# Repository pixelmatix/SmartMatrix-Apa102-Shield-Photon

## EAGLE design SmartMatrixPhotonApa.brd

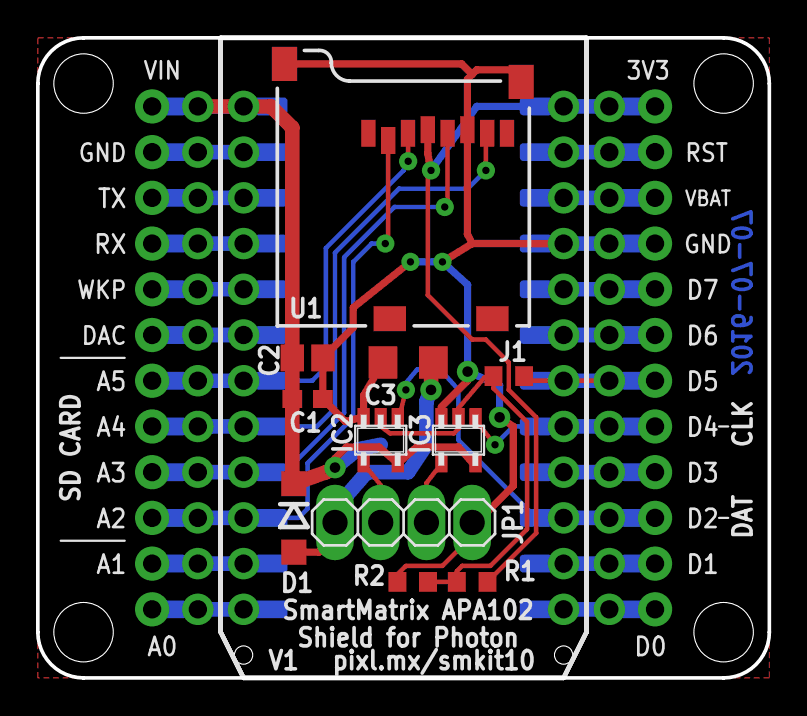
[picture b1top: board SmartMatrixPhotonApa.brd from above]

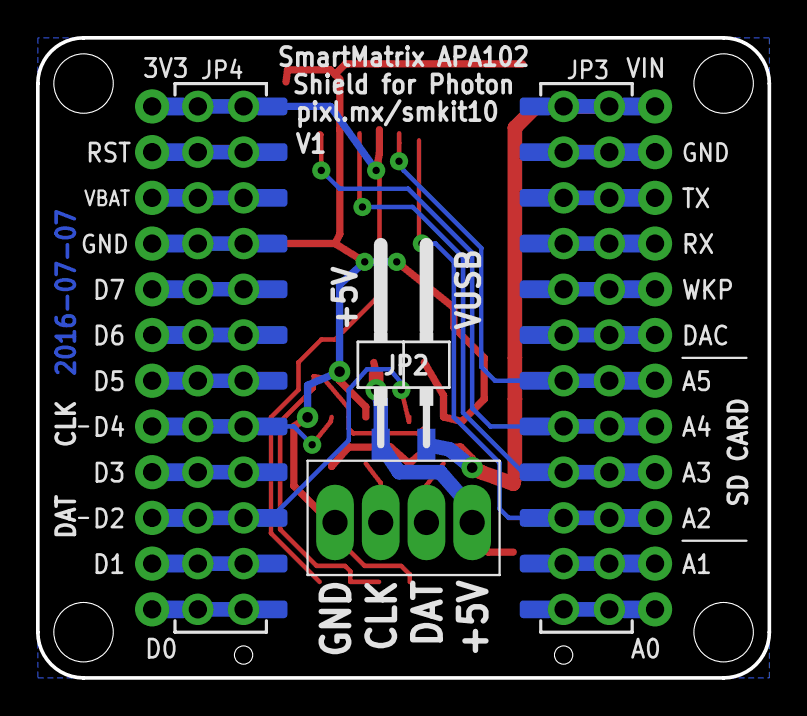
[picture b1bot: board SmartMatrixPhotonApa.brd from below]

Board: 2 copper layers, 40.6 x 35.6 mm, 14 parts (3 on the bottom side), 28 nets.

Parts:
C1: 0.1uF; C0603
C2: 10uF; C0805
C3: 100uF; C1206
D1: MBR0520LT; SOD123
IC1, IC2: 74AHC1G08DBV; SOT23-5
J1: 0-DNP; R0603
JP1: 1X04-LARGEHOLE
JP2: 1X02SMD/90
JP3: 2x12 Female SMT Socket; PHOTON_DUAL_HEADER_SHIELD_BOT_MOUNT_LEFT
JP4: 2x12 Female SMT Socket; PHOTON_DUAL_HEADER_SHIELD_BOT_MOUNT_RIGHT
R1: 47k; R0603
R2: 47k-DNP; R0603
U1: microSD; MICRO-SD-SOCKET-PP

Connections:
3V3: JP4.1, JP4.2, JP4.3V3, R1.1, U1.4
CLK: IC2.4, JP1.3
DAT: IC1.4, JP1.2
GND: C1.2, C2.2, C3.2, IC1.3, IC2.3, JP1.4, JP4.7, JP4.8, JP4.GND@2, R2.2, U1.6, U1.GND1, U1.GND2
LED_CLK: IC2.1, JP4.15, JP4.16, JP4.D4
LED_DAT: IC1.1, JP4.19, JP4.20, JP4.D2
LED_EN: J1.1, JP4.13, JP4.14, JP4.D5
unnamed: JP3.3, JP3.4, JP3.GND@0
unnamed: JP3.5, JP3.6, JP3.TX
unnamed: JP3.7, JP3.8, JP3.RX
unnamed: IC1.2, IC2.2, J1.2, R1.2, R2.1
unnamed: JP3.9, JP3.10, JP3.WKP
unnamed: JP3.11, JP3.12, JP3.DAC
unnamed: JP3.21, JP3.22, JP3.A1
unnamed: JP3.23, JP3.24, JP3.A0
unnamed: JP4.3, JP4.4, JP4.RST
unnamed: JP4.5, JP4.6, JP4.VBAT
unnamed: JP4.9, JP4.10, JP4.D7
unnamed: JP4.11, JP4.12, JP4.D6
unnamed: JP4.17, JP4.18, JP4.D3
unnamed: JP4.21, JP4.22, JP4.D1
unnamed: JP4.23, JP4.24, JP4.D0
SD_CS: JP3.19, JP3.20, JP3.A2, U1.2
SPI_MISO: JP3.15, JP3.16, JP3.A4, U1.7
SPI_MOSI: JP3.13, JP3.14, JP3.A5, U1.3
SPI_SCK: JP3.17, JP3.18, JP3.A3, U1.5
VEXT: C3.1, D1.A, JP1.1, JP2.1
VIN: C1.1, C2.1, D1.C, IC1.5, IC2.5, JP2.2, JP3.1, JP3.2, JP3.VIN

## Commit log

2016-04-19 Schematic cleaned up, mostly done, one todo
2016-04-19 Rough routing of board, not close to passing DRC
2016-04-19 add PDFs
2016-04-27 Rev V0.1, ready to order prototypes
2016-04-27 update PDFs
2016-04-27 Add BOM
2016-04-27 Add implied "1" quantities
2016-07-07 Changes for V1 - Larger holes for APA102 wires - a 1x2 SMT jumper on bottom side of board for VIN and VEXT - optional (DNP) 6.3V 100uF smd 1206 cap to shield to help with USB power kickback when long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
2016-07-07 Added Eagle files with V1 name and gerbers

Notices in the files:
SmartMatrixPhotonApa.brd:
Photon Shield Footprint originally by SparkFun, CC BY-SA 4.0
Pixelmatix 2016 CC BY-SA 4.0
